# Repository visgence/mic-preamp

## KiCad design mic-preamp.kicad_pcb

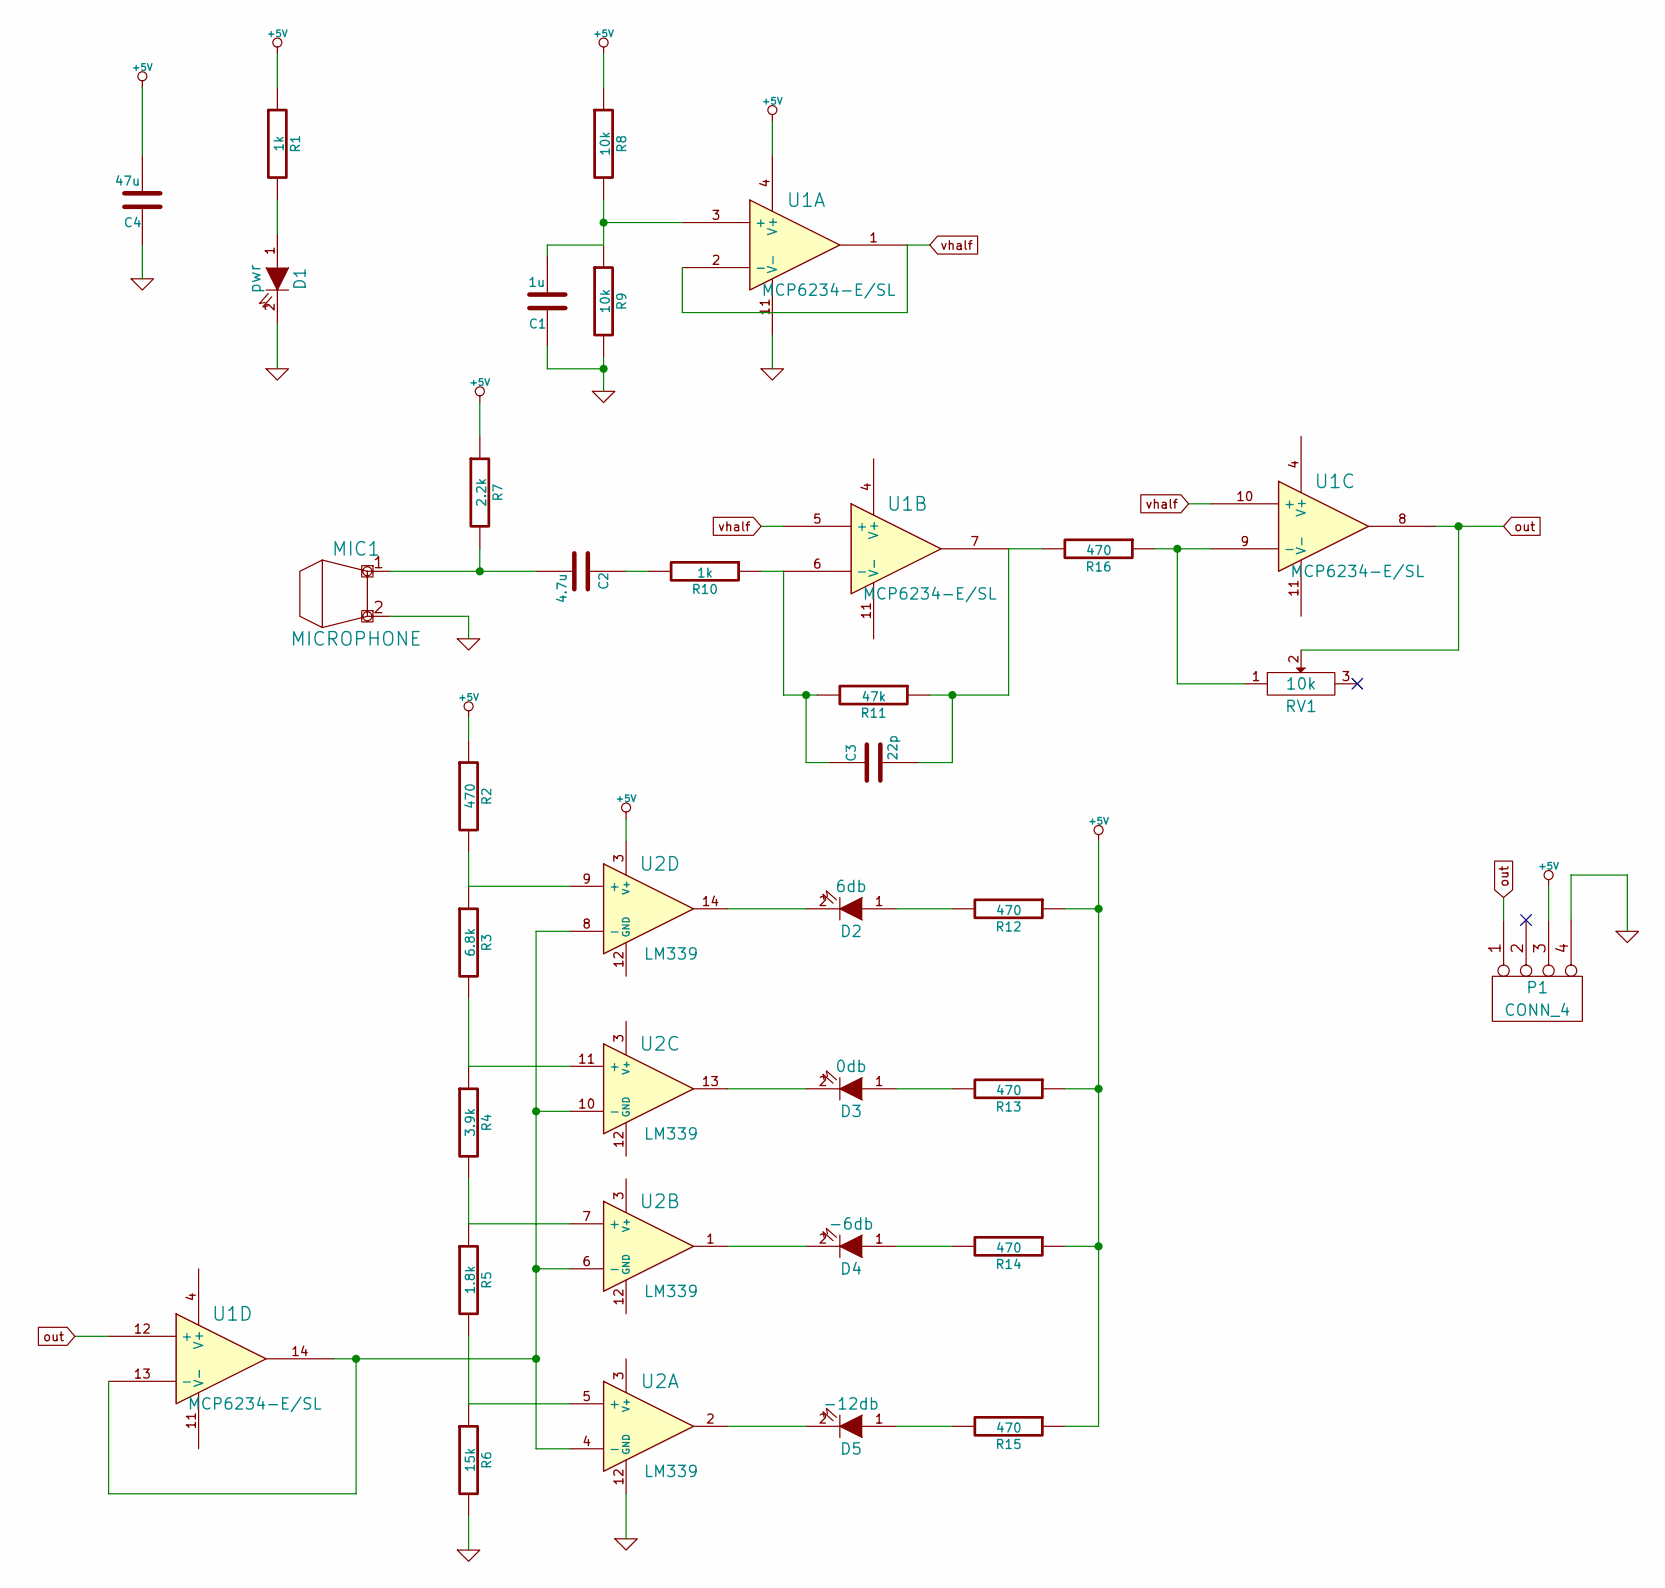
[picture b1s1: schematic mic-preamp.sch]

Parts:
C1: 1u; SM0603_Capa_VIS
C2: 4.7u; SM0603_Capa_VIS
C3: 22p; SM0603_Capa_VIS
C4: 47u; SM1206POL_VIS
D1: pwr; LED-0603
D2: 6db; LED-0603
D3: 0db; LED-0603
D4: -6db; LED-0603
D5: -12db; LED-0603
MIC1: MICROPHONE; MIC9.7
P1: CONN_4; bornier4
R1, R10: 1k; SM0603_VIS
R2, R12, R13, R14, R15, R16: 470; SM0603_VIS
R3: 6.8k; SM0603_VIS
R4: 3.9k; SM0603_VIS
R5: 1.8k; SM0603_VIS
R6: 15k; SM0603_VIS
R7: 2.2k; SM0603_VIS
R8, R9: 10k; SM0603_VIS
R11: 47k; SM0603_VIS
RV1: 10k; TC33X-2
U1: MCP6234-E/SL; SO14E
U2: LM339; SO14E

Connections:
+5V: C4.2, P1.3, R1.1, R2.1, R7.1, R8.1, R12.1, R13.1, R14.1, R15.1, U1.4 (V+), U2.3 (V+)
GND: C1.1, C4.1, D1.2 (K), MIC1.2 (MIC-), P1.4, R6.2, R9.2, U1.11 (V-), U2.12 (GND)
unnamed: C1.2, R8.2, R9.1, U1.3 (+)
unnamed: C2.1, R10.2
unnamed: C2.2, MIC1.1 (MIC+), R7.2
unnamed: C3.1, R10.1, R11.2, U1.6 (-)
unnamed: C3.2, R11.1, R16.2, U1.7
unnamed: D1.1 (A), R1.2
unnamed: D2.1 (A), R12.2
unnamed: D2.2 (K), U2.14
unnamed: D3.1 (A), R13.2
unnamed: D3.2 (K), U2.13
unnamed: D4.1 (A), R14.2
unnamed: D4.2 (K), U2.1
unnamed: D5.1 (A), R15.2
unnamed: D5.2 (K), U2.2
unnamed: R2.2, R3.1, U2.9 (+)
unnamed: R3.2, R4.1, U2.11 (+)
unnamed: R4.2, R5.1, U2.7 (+)
unnamed: R5.2, R6.1, U2.5 (+)
unnamed: R16.1, RV1.1, U1.9 (-)
unnamed: U1.13 (-), U1.14, U2.4 (-), U2.6 (-), U2.8 (-), U2.10 (-)
out: P1.1, RV1.2, U1.8, U1.12 (+)
vhalf: U1.1, U1.2 (-), U1.5 (+), U1.10 (+)

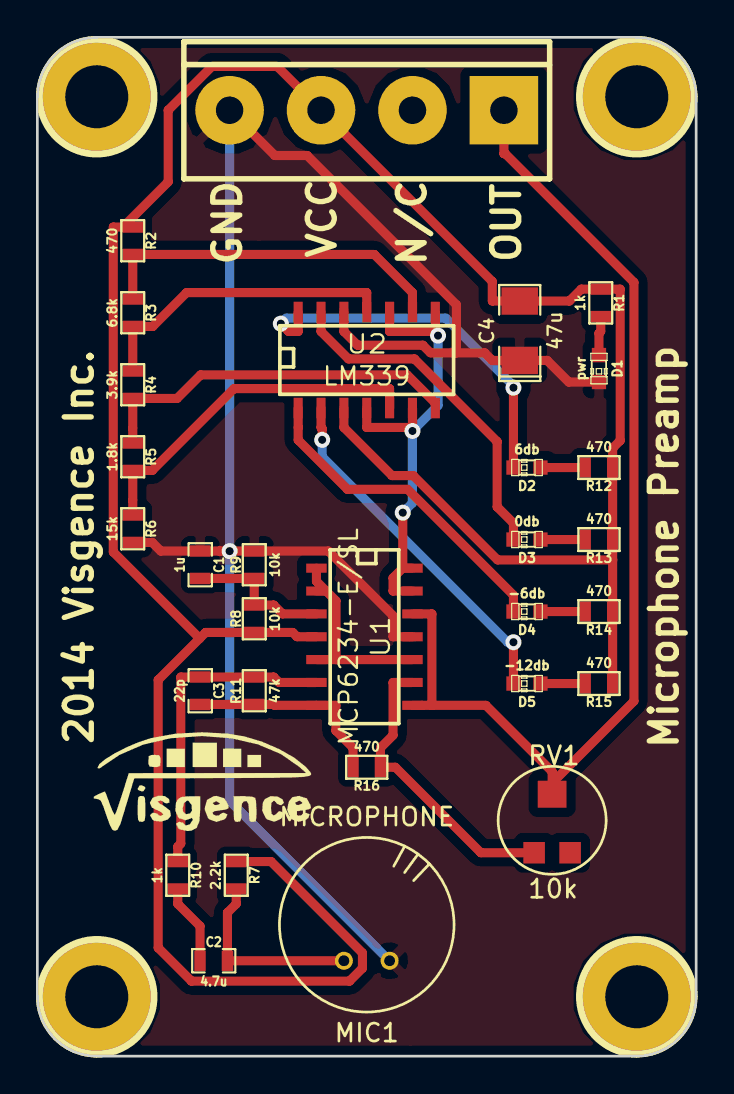
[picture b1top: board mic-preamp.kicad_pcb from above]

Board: 2 copper layers, 36.6 x 56.6 mm, 35 parts (0 on the bottom side), 24 nets.

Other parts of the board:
G1: LOGO
h1, h2, h3, h4: pin; 1pin_C

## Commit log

2014-08-06 Started working on pcb
2014-08-07 Routed and generated gerber
2014-08-07 Fixed solder mask
2014-09-03 resized board, change gain
2014-09-03 re-routed board
